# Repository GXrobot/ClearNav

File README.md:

GitHub Repository for Capstone Project of ClearNav Team
```
Members Include:
Spencer Lall
William Xue
Muhammad Ahmed Ather
William Huong
Namsakhi Kumar
Taimoor Ahmed
```

Spring - Summer 2022 Engineering Science Capstone Project

EZhud is a convenient heads up display motorcycle riders that features
built-in navigation, speed limit display and helmet mounted dashcam.

In this repository contains the code for the webserver, raspberry pi internal scripts
3D printed designs and GPS tracking code. 

EZhud is easy to use and and presents a simple interface for the user. Any information is presented in a heads up display above the riders right eye.

The following image shows the system overview of the EZhud device.

Here is a final product image on a full-face helmet.

The following is the Youtube video of the project.

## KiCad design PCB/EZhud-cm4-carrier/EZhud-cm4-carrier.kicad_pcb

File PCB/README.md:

PCB Design for EZhud Motorcycle Project

```
Lead by:
Muhammad Ahmed Ather
Taimoor Ahmed
```

PCB design is compact and meant to be connected to the Raspberry Pi CM4 board, featuring
all the ports necessary for our project. Including RPi CM4 Hirose connectors, high speed USB,
SD card slot, GPIO connectors, mini-HDMI connector, USB-C power connector and the RPi Cam
interface

Work is still in progress! PCB still needs some tweaking to be fully functional. 

This image shows the front of the PCB design.

This image shows the back of the PCB design.

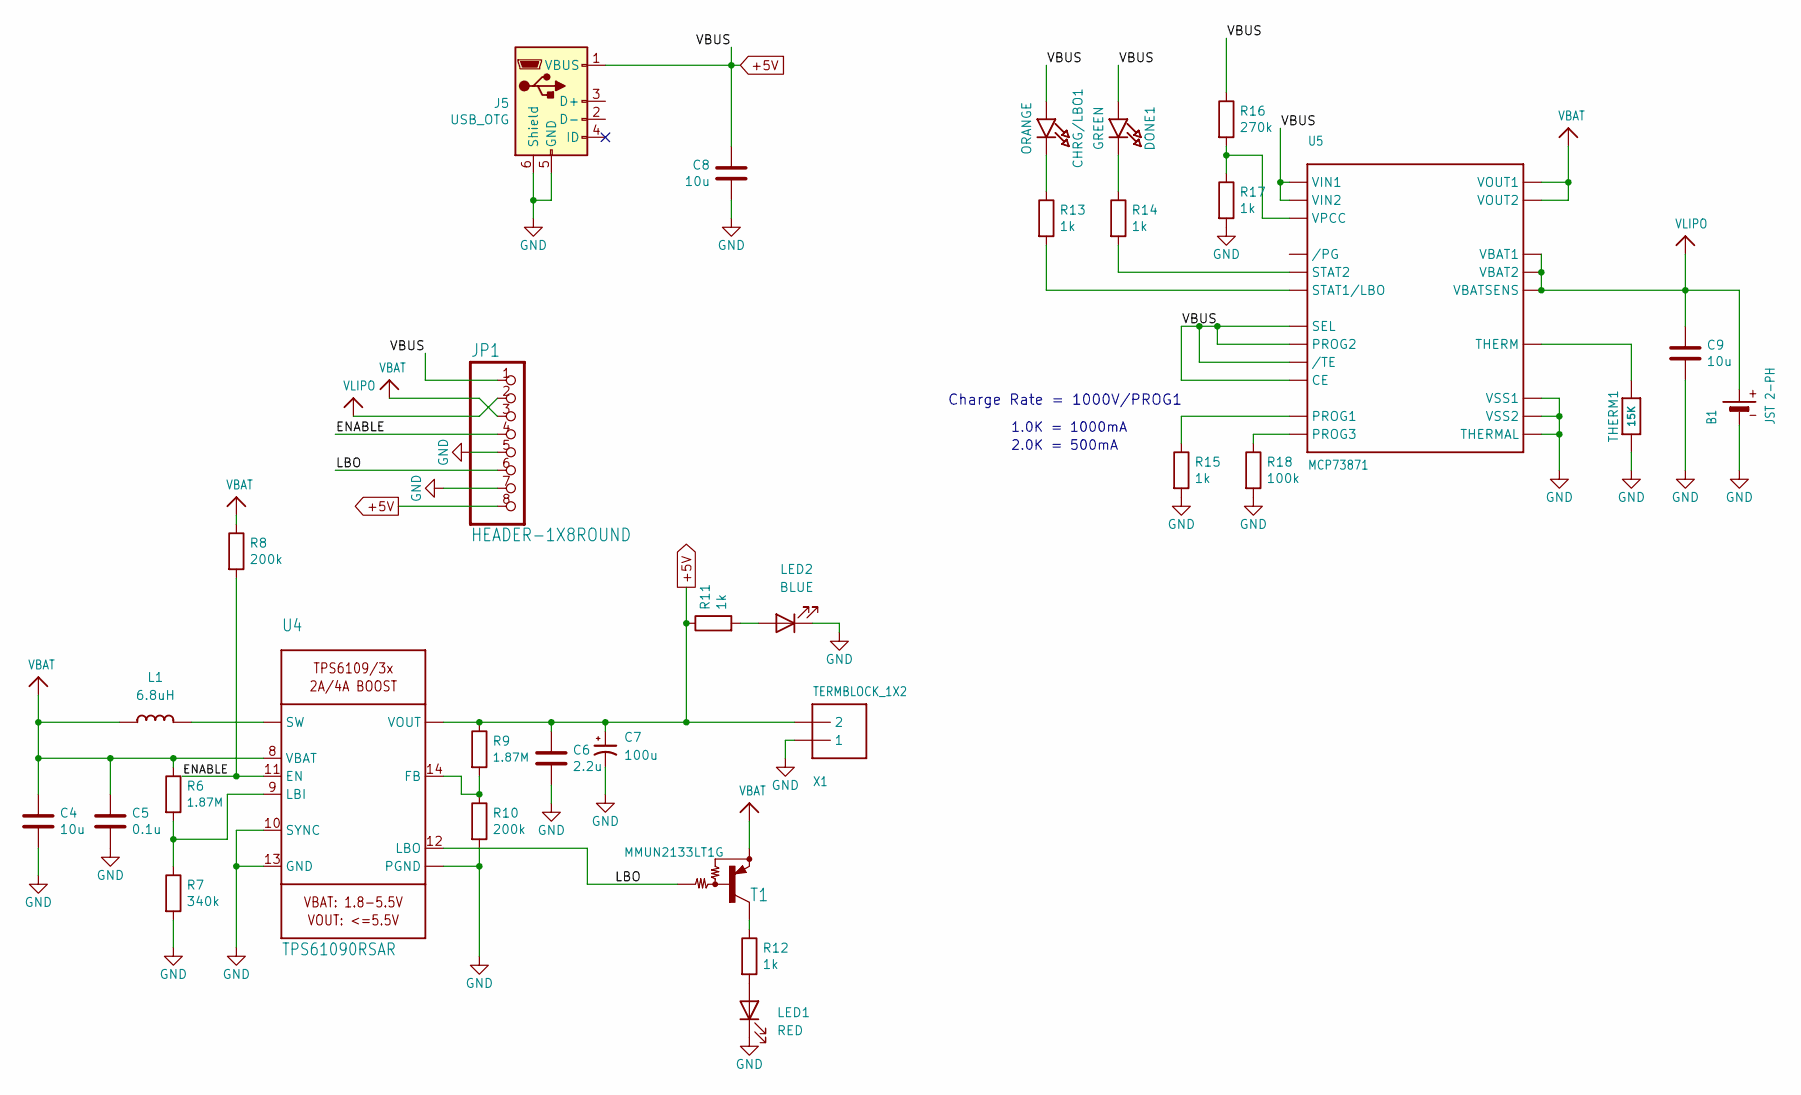
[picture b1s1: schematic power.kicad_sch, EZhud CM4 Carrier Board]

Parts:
B1: JST 2-PH; JSTPH2
C4, C8, C9: 10u; C_0805_2012Metric; Part Description 10uF 10% 10V Ceramic Capacitor X7R 0805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
C5: 0.1u; C_0805_2012Metric; Part Description 10uF 10% 10V Ceramic Capacitor X7R 0805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
C6: 2.2u; C_0805_2012Metric; Part Description 10uF 10% 10V Ceramic Capacitor X7R 0805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
C7: 100u; C_1210_3225Metric
CHRG/LBO1: ORANGE; CHIPLED_0805_NOOUTLINE
DONE1: GREEN; CHIPLED_0805_NOOUTLINE
J5: USB_OTG; USB_Micro-B_EDAC_UCON00686; Part Description USB - micro B USB 2.0 Receptacle Connec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
JP1: HEADER-1X8ROUND; 1X08_ROUND
L1: 6.8uH; INDUCTOR_5X5MM_TDK_VLC5045
LED1: RED; LED_0805_2012Metric
LED2: BLUE; LED_0805_2012Metric
R6, R9: 1.87M; R_0805_2012Metric
R7: 340k; R_0805_2012Metric
R8, R10: 200k; R_0805_2012Metric
R11, R12, R13, R14, R15, R17: 1k; R_0402_1005Metric; Part Description Resistor 1K M1005 1% 63mW
R16: 270k; R_0402_1005Metric; Part Description Resistor 1K M1005 1% 63mW
R18: 100k; R_0402_1005Metric; Part Description Resistor 1K M1005 1% 63mW
T1: MMUN2133LT1G; SC59-BEC
THERM1: 15K; 0805-NO
U4: TPS61090RSAR; PVQFN-16
U5: MCP73871; QFN20_4MM
X1: TERMBLOCK_1X2; TERMBLOCK_1X2-3.5MM

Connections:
+5V: C6.1, C7.1, C8.1, CHRG/LBO1.A, DONE1.A, J5.1 (VBUS), JP1.1, JP1.8, R9.1, R11.1, R16.1, U4.1 (VOUT), U4.15 (VOUT), U4.16 (VOUT), U5.P$3 (SEL), U5.P$4 (PROG2), U5.P$9 (/TE), U5.P$17 (CE), U5.P$18 (VIN1), U5.P$19 (VIN2), X1.2; also elsewhere on the board
/Power Boost/ENABLE: JP1.4, R8.2, U4.11 (EN)
/Power Boost/LBO: JP1.6, T1.B, U4.12 (LBO)
GND: B1.1 (-), C4.2, C5.2, C6.2, C7.2, C8.2, C9.2, J5.5 (GND), J5.6 (Shield), JP1.5, JP1.7, LED1.1 (K), LED2.1 (K), R7.2, R10.2, R15.2, R17.2, R18.2, THERM1.1, U4.5 (PGND), U4.6 (PGND), U4.7 (PGND), U4.10 (SYNC), U4.13 (GND), U4.P$18 (PGND), U4.P$19 (PGND), U4.P$20 (PGND), U4.P$21 (PGND), U4.P$22 (PGND), U4.THERMAL (PGND), U5.P$10 (VSS1), U5.P$11 (VSS2), U5.P$21 (THERMAL), X1.1; also elsewhere on the board
unnamed: CHRG/LBO1.C, R13.1
unnamed: DONE1.C, R14.1
unnamed: L1.P$2 (2), U4.3 (SW), U4.4 (SW)
unnamed: LED1.2 (A), R12.2
unnamed: LED2.2 (A), R11.2
unnamed: R6.2, R7.1, U4.9 (LBI)
unnamed: R9.2, R10.1, U4.14 (FB)
unnamed: R12.1, T1.C
unnamed: R13.2, U5.P$8 (STAT1/LBO)
unnamed: R14.2, U5.P$7 (STAT2)
unnamed: R15.1, U5.P$13 (PROG1)
unnamed: R16.2, R17.1, U5.P$2 (VPCC)
unnamed: R18.1, U5.P$12 (PROG3)
unnamed: THERM1.2, U5.P$5 (THERM)
VBAT: C4.1, C5.1, JP1.3, L1.P$1 (1), R6.1, R8.1, T1.E, U4.8 (VBAT), U5.P$1 (VOUT1), U5.P$20 (VOUT2)
VLIPO: B1.2 (+), C9.1, JP1.2, U5.P$14 (VBAT1), U5.P$15 (VBAT2), U5.P$16 (VBATSENS)

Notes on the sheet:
2.0K = 500mA
Charge Rate = 1000V/PROG1
1.0K = 1000mA

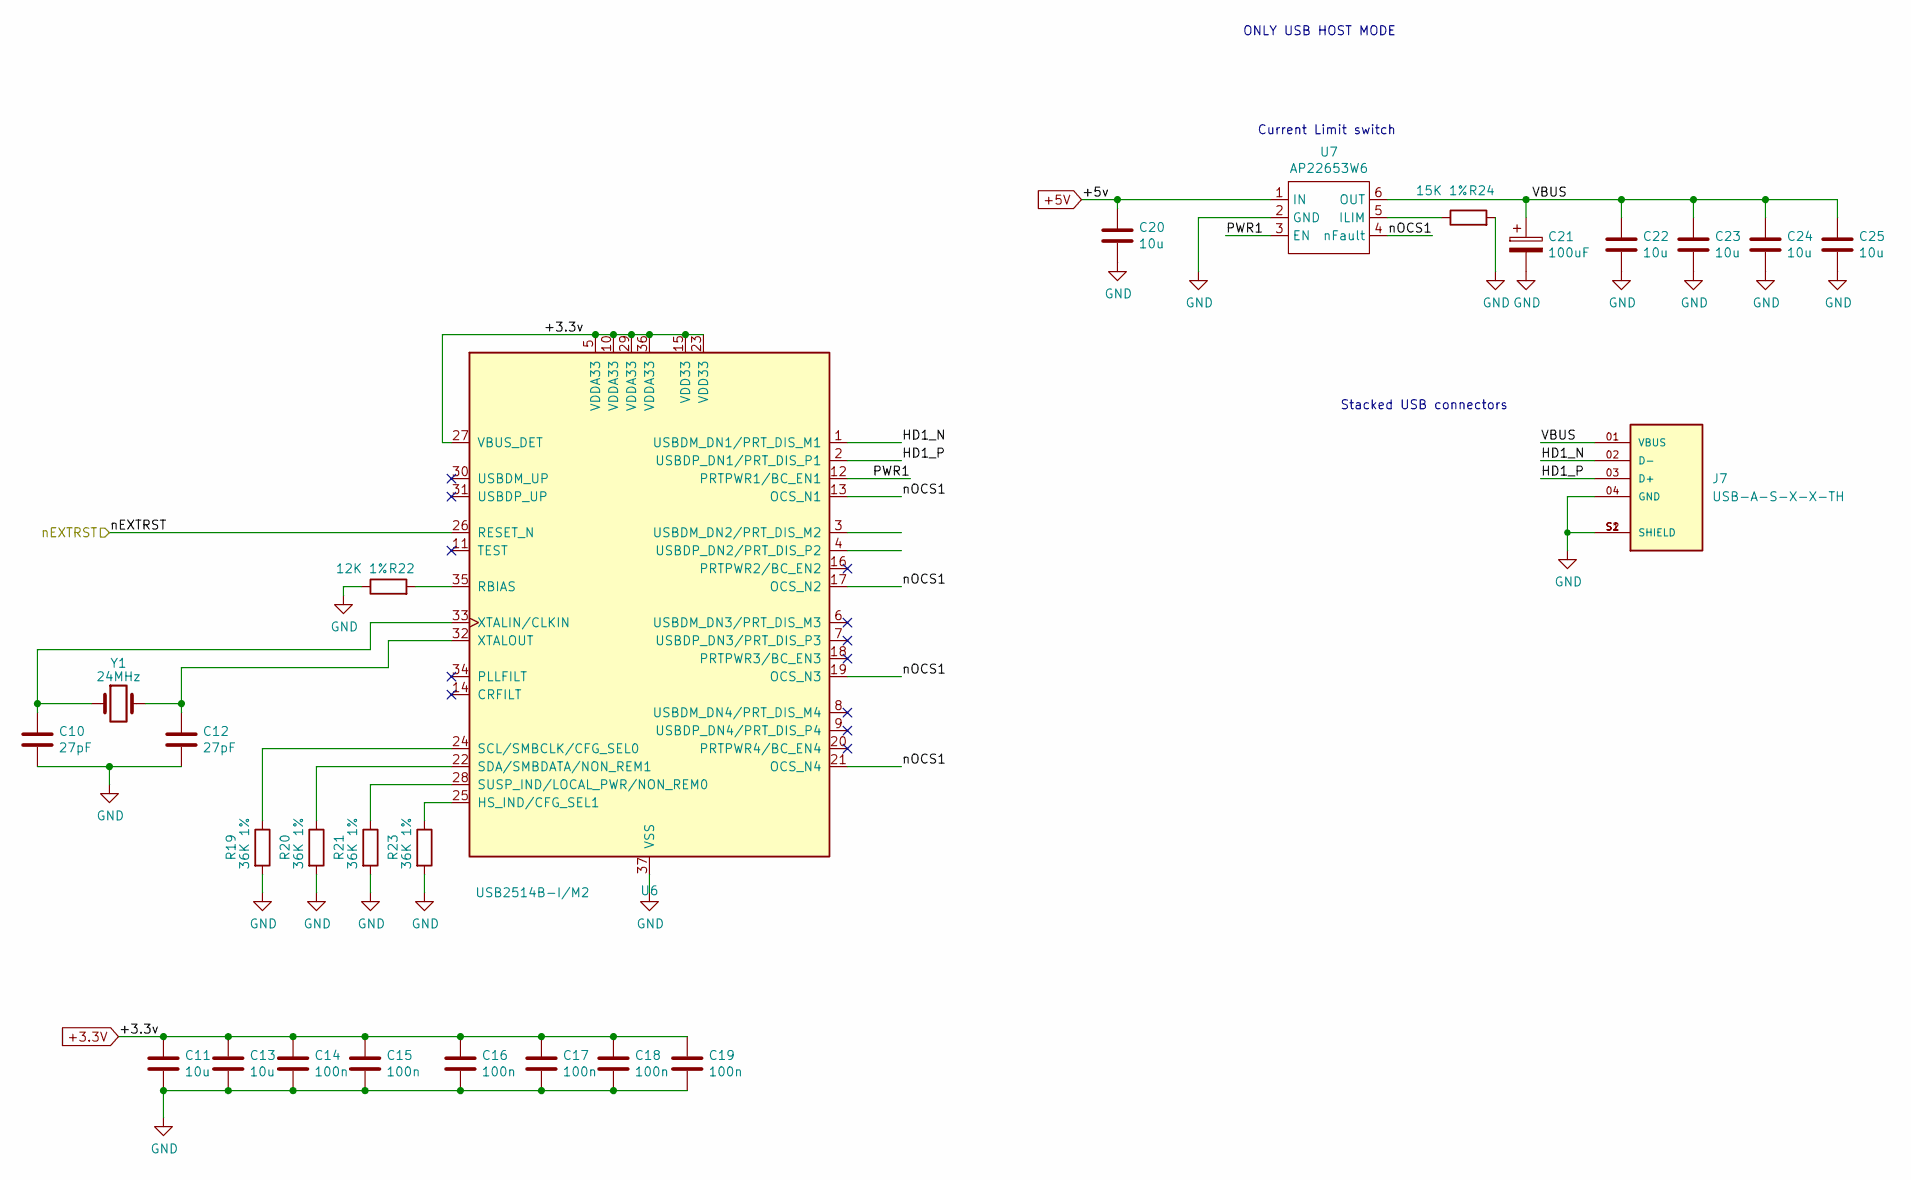
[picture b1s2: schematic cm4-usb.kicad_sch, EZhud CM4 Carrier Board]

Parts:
C10, C12: 27pF; C_0402_1005Metric; Part Description 27pF 5% 50V Ceramic Capacitor C0G, NP0 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
C11, C13, C20, C22, C23, C24, C25: 10u; C_0805_2012Metric; Part Description 10uF 10% 10V Ceramic Capacitor X7R 0805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
C14, C15, C16, C17, C18, C19: 100n; C_0402_1005Metric; Part Description 0.1uF 10% 16V Ceramic Capacitor X7R 040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
C21: 100uF; CP_EIA-7343-31_Kemet-D; Part Description Capacitor, SP-Cap, 100u, 6.3V, 15mR ESR
J7: USB-A-S-X-X-TH; SAMTEC_USB-A-S-X-X-TH; PARTREV R
R19, R20, R21, R23: 36K 1%; R_0402_1005Metric; Part Description Resistor 36K M1005 1% 63mW
R22: 12K 1%; R_0402_1005Metric; Part Description Resistor 12K M1005 1% 63mW
R24: 15K 1%; R_0402_1005Metric; Part Description Resistor 15K M1005 1% 63mW
U6: USB2514B-I/M2; QFN-36-1EP_6x6mm_P0.5mm_EP3.7x3.7mm; Part Description USB Hub Controller USB Interface 36-SQF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
U7: AP22653W6; SOT-23-6; Part Description Power Switch/Driver 1:1 P-Channel 2.1A 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
Y1: 24MHz; Crystal_SMD_HC49-SD; Part Description 24MHz Crystal 18pf 30ppm 30ppm

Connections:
+3.3V: C11.1, C13.1, C14.1, C15.1, C16.1, C17.1, C18.1, C19.1, U6.5 (VDDA33), U6.10 (VDDA33), U6.15 (VDD33), U6.23 (VDD33), U6.27 (VBUS_DET), U6.29 (VDDA33), U6.36 (VDDA33); also elsewhere on the board
+5V: C20.1, U7.1 (IN); also elsewhere on the board
/CM4 USB/HD1_N: J7.02 (D-), U6.1 (USBDM_DN1/PRT_DIS_M1)
/CM4 USB/HD1_P: J7.03 (D+), U6.2 (USBDP_DN1/PRT_DIS_P1)
/CM4 USB/PWR1: U6.12 (PRTPWR1/BC_EN1), U7.3 (EN)
/CM4 USB/VBUS: C21.1, C22.1, C23.1, C24.1, C25.1, J7.01 (VBUS), U7.6 (OUT)
/CM4 USB/nEXTRST: U6.26 (RESET_N)
/CM4 USB/nOCS1: U6.13 (OCS_N1), U6.17 (OCS_N2), U6.19 (OCS_N3), U6.21 (OCS_N4), U7.4 (nFault)
GND: C10.2, C11.2, C12.2, C13.2, C14.2, C15.2, C16.2, C17.2, C18.2, C19.2, C20.2, C21.2, C22.2, C23.2, C24.2, C25.2, J7.04 (GND), J7.S1 (SHIELD), J7.S2 (SHIELD), R19.2, R20.2, R21.2, R22.1, R23.2, R24.2, U6.37 (VSS), U7.2 (GND); also elsewhere on the board
unnamed: C10.1, U6.33 (XTALIN/CLKIN), Y1.1
unnamed: C12.1, U6.32 (XTALOUT), Y1.2
unnamed: R19.1, U6.24 (SCL/SMBCLK/CFG_SEL0)
unnamed: R20.1, U6.22 (SDA/SMBDATA/NON_REM1)
unnamed: R21.1, U6.28 (SUSP_IND/LOCAL_PWR/NON_REM0)
unnamed: R22.2, U6.35 (RBIAS)
unnamed: R23.1, U6.25 (HS_IND/CFG_SEL1)
unnamed: R24.1, U7.5 (ILIM)

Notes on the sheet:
Current Limit switch
Stacked USB connectors
ONLY USB HOST MODE

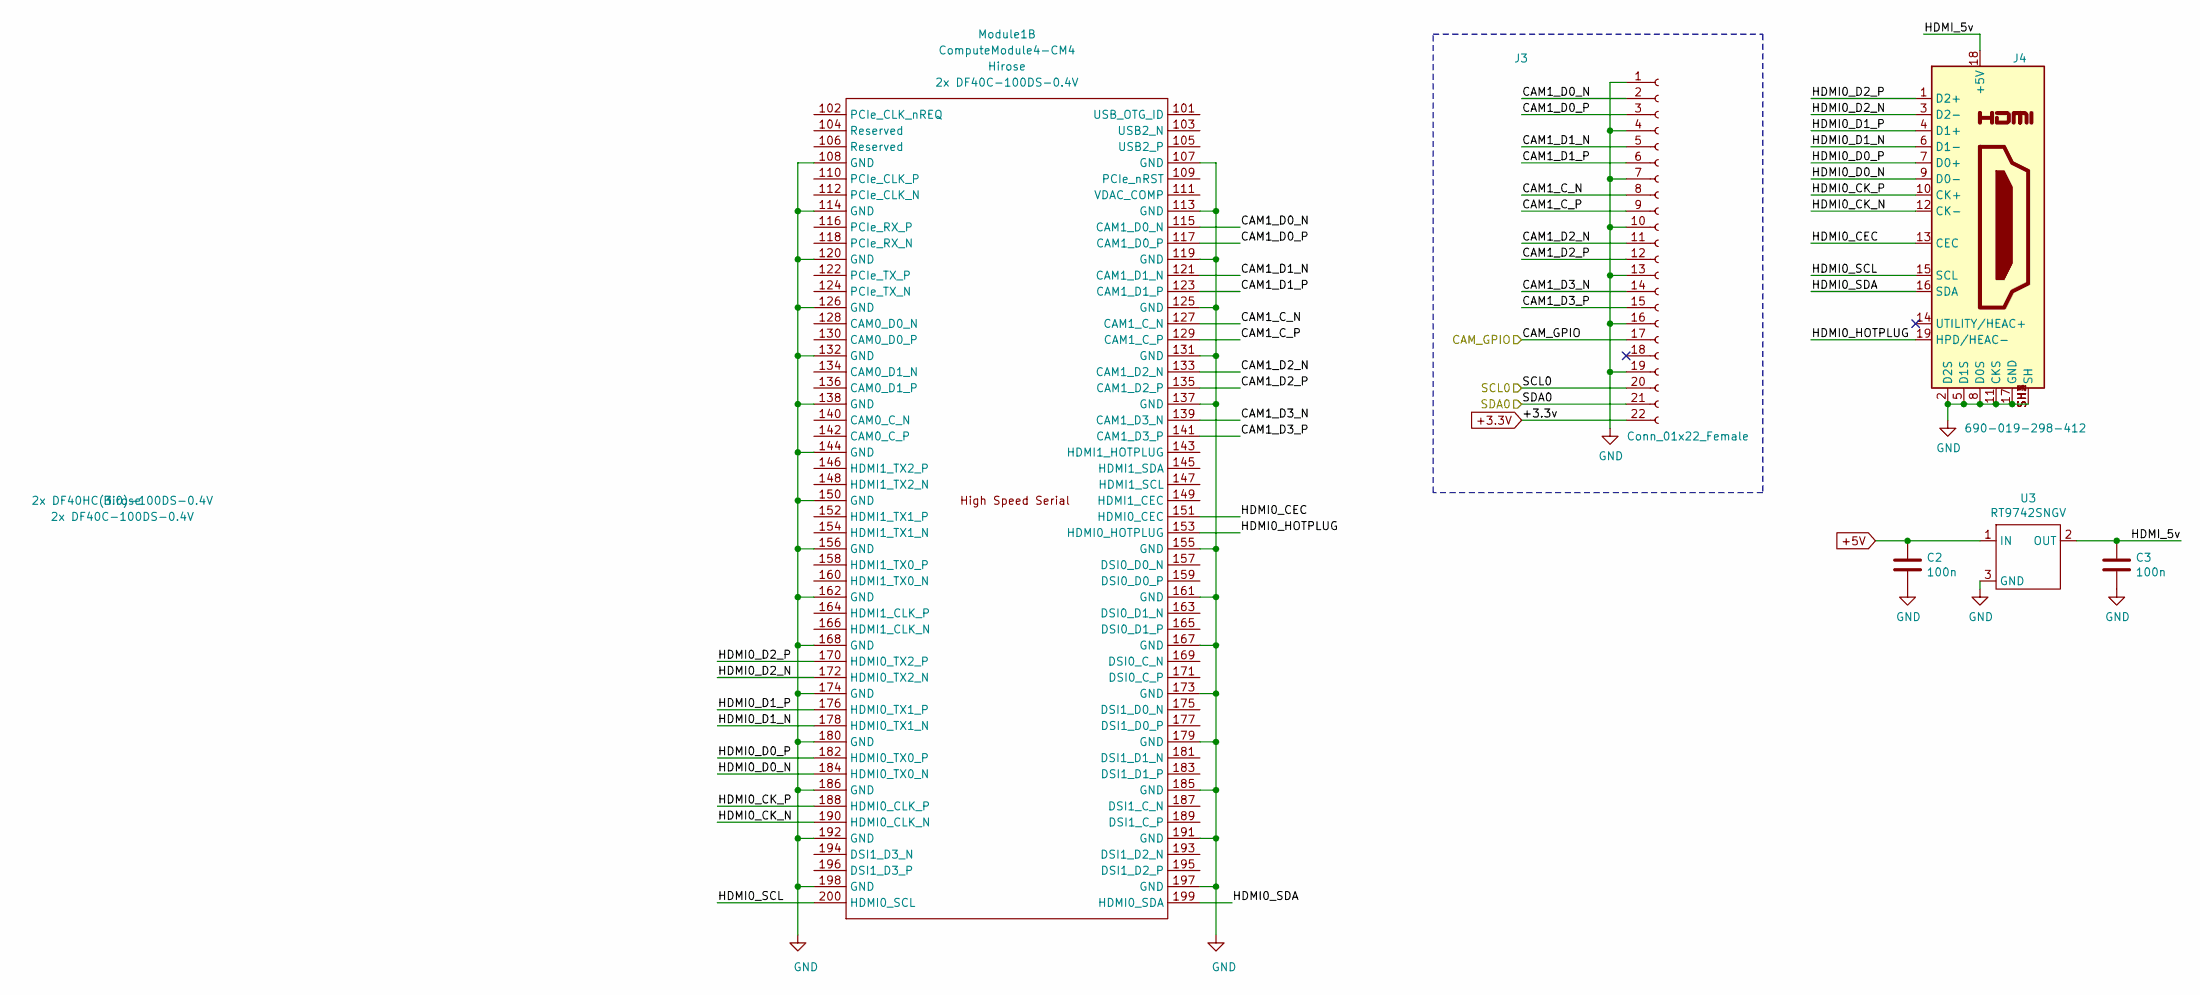
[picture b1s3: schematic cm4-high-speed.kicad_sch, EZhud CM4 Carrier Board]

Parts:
C2, C3: 100n; C_0402_1005Metric; Part Description 0.1uF 10% 16V Ceramic Capacitor X7R 040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
J3: Conn_01x22_Female; Hirose_FH12-22S-0.5SH_1x22-1MP_P0.50mm_Horizontal; Part Description 22 Position FFC, FPC Connector Contacts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
J4: 690-019-298-412; EDAC 690-019-298-412; Part Description HDMI Connector, Right Angle, 19 Contact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
Module1: ComputeModule4-CM4; Raspberry-Pi-4-Compute-Module; MPN 2x DF40C-100DS-0.4V; Digi-Key_PN 2x H11615CT-ND
U3: RT9742SNGV; SOT-23; Part Description Power Switch/Driver 1:1 N-Channel 500mA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

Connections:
+3.3V: J3.22; also elsewhere on the board
+5V: C2.1, U3.1 (IN); also elsewhere on the board
/CM4 High Speed/CAM1_C_N: J3.8, Module1.127 (CAM1_C_N)
/CM4 High Speed/CAM1_C_P: J3.9, Module1.129 (CAM1_C_P)
/CM4 High Speed/CAM1_D0_N: J3.2, Module1.115 (CAM1_D0_N)
/CM4 High Speed/CAM1_D0_P: J3.3, Module1.117 (CAM1_D0_P)
/CM4 High Speed/CAM1_D1_N: J3.5, Module1.121 (CAM1_D1_N)
/CM4 High Speed/CAM1_D1_P: J3.6, Module1.123 (CAM1_D1_P)
/CM4 High Speed/CAM1_D2_N: J3.11, Module1.133 (CAM1_D2_N)
/CM4 High Speed/CAM1_D2_P: J3.12, Module1.135 (CAM1_D2_P)
/CM4 High Speed/CAM1_D3_N: J3.14, Module1.139 (CAM1_D3_N)
/CM4 High Speed/CAM1_D3_P: J3.15, Module1.141 (CAM1_D3_P)
/CM4 High Speed/CAM_GPIO: J3.17; also elsewhere on the board
/CM4 High Speed/HDMI0_CEC: J4.13 (CEC), Module1.151 (HDMI0_CEC)
/CM4 High Speed/HDMI0_CK_N: J4.12 (CK-), Module1.190 (HDMI0_CLK_N)
/CM4 High Speed/HDMI0_CK_P: J4.10 (CK+), Module1.188 (HDMI0_CLK_P)
/CM4 High Speed/HDMI0_D0_N: J4.9 (D0-), Module1.184 (HDMI0_TX0_N)
/CM4 High Speed/HDMI0_D0_P: J4.7 (D0+), Module1.182 (HDMI0_TX0_P)
/CM4 High Speed/HDMI0_D1_N: J4.6 (D1-), Module1.178 (HDMI0_TX1_N)
/CM4 High Speed/HDMI0_D1_P: J4.4 (D1+), Module1.176 (HDMI0_TX1_P)
/CM4 High Speed/HDMI0_D2_N: J4.3 (D2-), Module1.172 (HDMI0_TX2_N)
/CM4 High Speed/HDMI0_D2_P: J4.1 (D2+), Module1.170 (HDMI0_TX2_P)
/CM4 High Speed/HDMI0_HOTPLUG: J4.19 (HPD/HEAC-), Module1.153 (HDMI0_HOTPLUG)
/CM4 High Speed/HDMI0_SCL: J4.15 (SCL), Module1.200 (HDMI0_SCL)
/CM4 High Speed/HDMI0_SDA: J4.16 (SDA), Module1.199 (HDMI0_SDA)
/CM4 High Speed/HDMI_5v: C3.1, J4.18 (+5V), U3.2 (OUT)
/CM4 High Speed/SCL0: J3.20; also elsewhere on the board
/CM4 High Speed/SDA0: J3.21; also elsewhere on the board
GND: C2.2, C3.2, J3.1, J3.4, J3.7, J3.10, J3.13, J3.16, J3.19, J4.2 (D2S), J4.5 (D1S), J4.8 (D0S), J4.11 (CKS), J4.17 (GND), J4.SH1 (SH), J4.SH2 (SH), J4.SH3 (SH), J4.SH4 (SH), Module1.107 (GND), Module1.108 (GND), Module1.113 (GND), Module1.114 (GND), Module1.119 (GND), Module1.120 (GND), Module1.125 (GND), Module1.126 (GND), Module1.131 (GND), Module1.132 (GND), Module1.137 (GND), Module1.138 (GND), Module1.144 (GND), Module1.150 (GND), Module1.155 (GND), Module1.156 (GND), Module1.161 (GND), Module1.162 (GND), Module1.167 (GND), Module1.168 (GND), Module1.173 (GND), Module1.174 (GND), Module1.179 (GND), Module1.180 (GND), Module1.185 (GND), Module1.186 (GND), Module1.191 (GND), Module1.192 (GND), Module1.197 (GND), Module1.198 (GND), U3.3 (GND); also elsewhere on the board

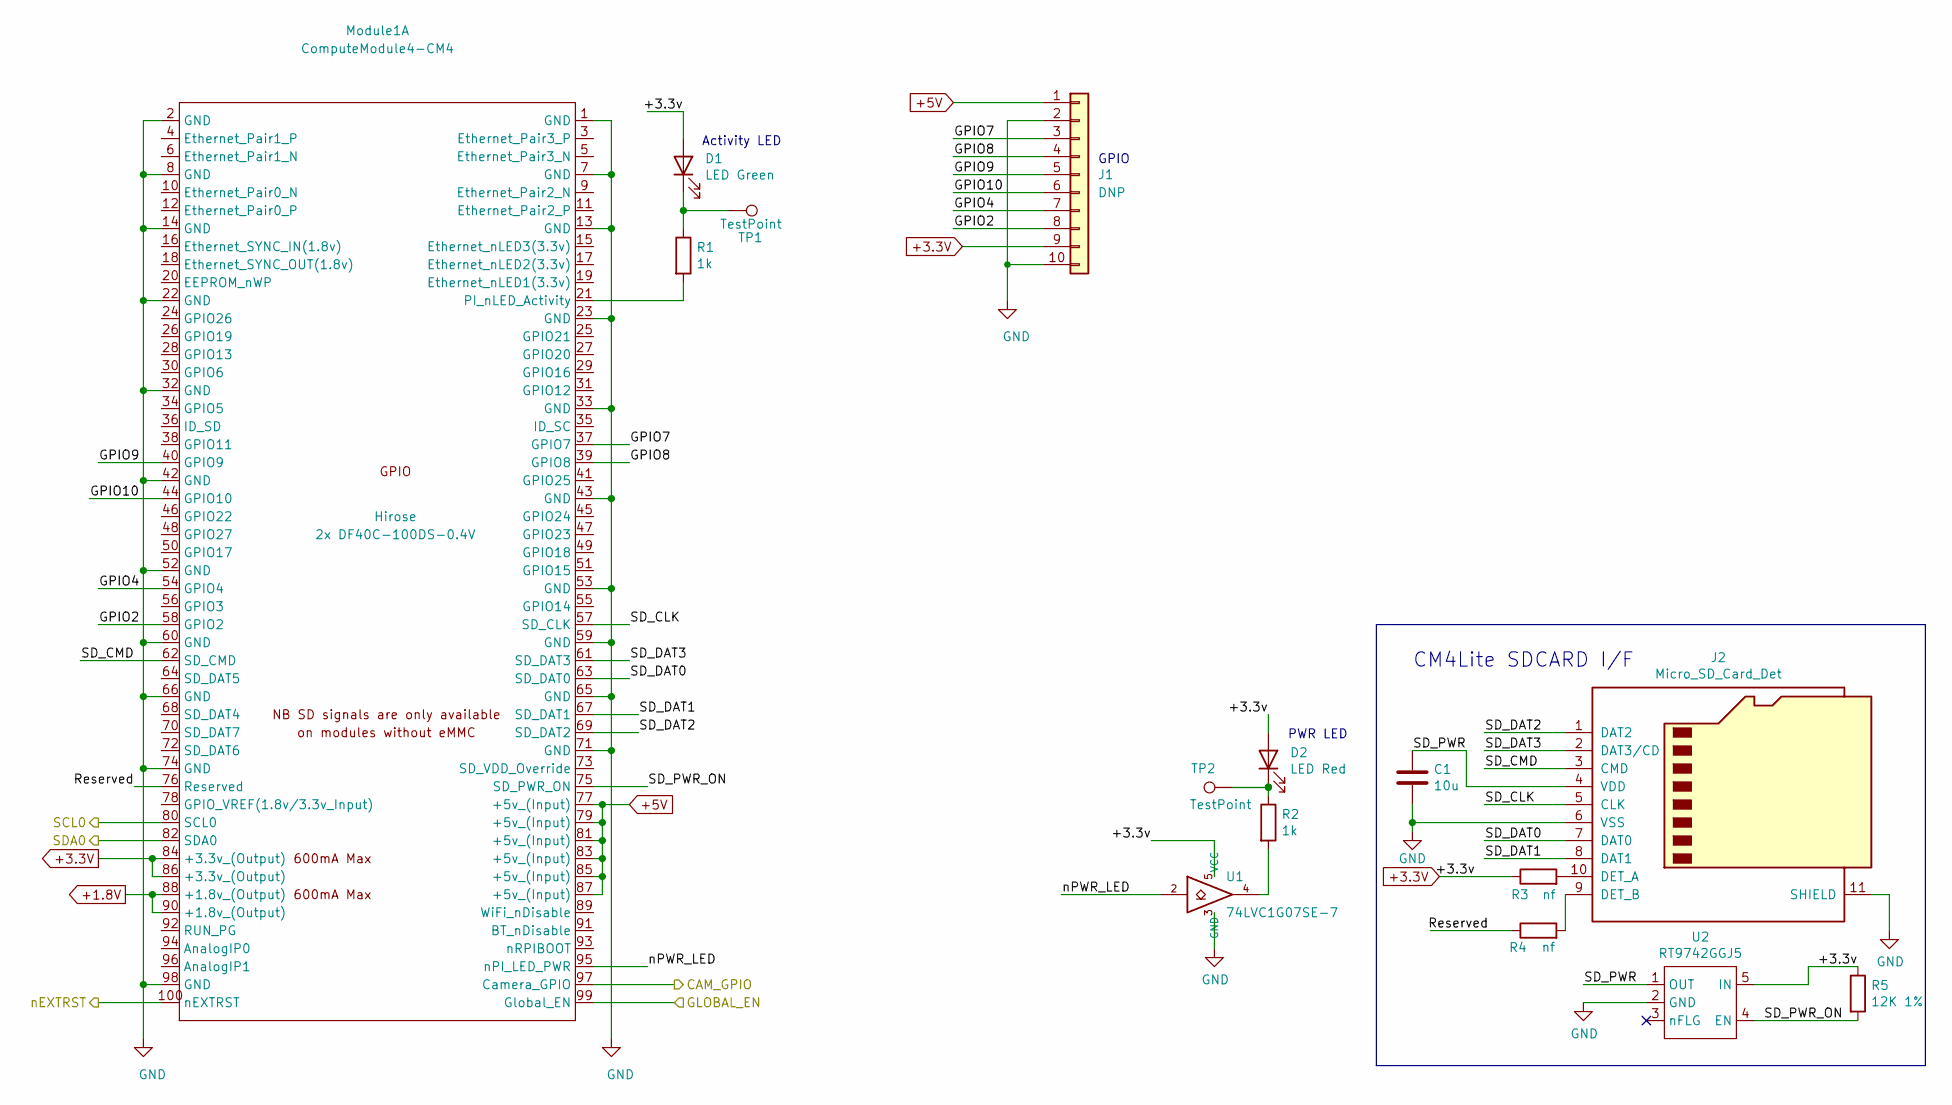
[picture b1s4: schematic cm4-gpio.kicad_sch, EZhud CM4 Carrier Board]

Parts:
C1: 10u; C_0805_2012Metric; Part Description 10uF 10% 10V Ceramic Capacitor X7R 0805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
D1: LED Green; LED_0603_1608Metric; Part Description Green 572nm LED Indication - Discrete 2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
D2: LED Red; LED_0603_1608Metric; Part Description Red 620nm LED Indication - Discrete 2.2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
J1: DNP; PinHeader_1x10_P2.54mm_Vertical
J2: Micro_SD_Card_Det; SDCARD_MOLEX_503398-1892; Part Description 9 (8 + 1) Position Card Connector micro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
Module1: ComputeModule4-CM4; Raspberry-Pi-4-Compute-Module; MPN 2x DF40C-100DS-0.4V; Digi-Key_PN 2x H11615CT-ND
R1, R2: 1k; R_0402_1005Metric; Part Description Resistor 1K M1005 1% 63mW
R3, R4: nf; R_0402_1005Metric; Part Description Resistor 1K M1005 1% 63mW
R5: 12K 1%; R_0402_1005Metric; Part Description Resistor 12K M1005 1% 63mW
TP1, TP2: TestPoint; TestPoint_Pad_2.0x2.0mm
U1: 74LVC1G07SE-7; SOT-353_SC-70-5; Part Description Buffer, Non-Inverting 1 Element 1 Bit p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
U2: RT9742GGJ5; SOT-23-5; Part Description Power Switch/Driver 1:1 N-Channel 1A TS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

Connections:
+1.8V: Module1.88 (+1.8v_(Output)), Module1.90 (+1.8v_(Output))
+3.3V: D1.2 (A), D2.2 (A), J1.9, Module1.84 (+3.3v_(Output)), Module1.86 (+3.3v_(Output)), R3.1, R5.1, U1.5 (VCC), U2.5 (IN); also elsewhere on the board
+5V: J1.1, Module1.77 (+5v_(Input)), Module1.79 (+5v_(Input)), Module1.81 (+5v_(Input)), Module1.83 (+5v_(Input)), Module1.85 (+5v_(Input)), Module1.87 (+5v_(Input)); also elsewhere on the board
/CM4 GPIO/GLOBAL_EN: Module1.99 (Global_EN)
/CM4 GPIO/GPIO2: J1.8, Module1.58 (GPIO2)
/CM4 GPIO/GPIO4: J1.7, Module1.54 (GPIO4)
/CM4 GPIO/GPIO7: J1.3, Module1.37 (GPIO7)
/CM4 GPIO/GPIO8: J1.4, Module1.39 (GPIO8)
/CM4 GPIO/GPIO9: J1.5, Module1.40 (GPIO9)
/CM4 GPIO/GPIO10: J1.6, Module1.44 (GPIO10)
/CM4 GPIO/Reserved: Module1.76 (Reserved), R4.1
/CM4 GPIO/SD_CLK: J2.5 (CLK), Module1.57 (SD_CLK)
/CM4 GPIO/SD_CMD: J2.3 (CMD), Module1.62 (SD_CMD)
/CM4 GPIO/SD_DAT0: J2.7 (DAT0), Module1.63 (SD_DAT0)
/CM4 GPIO/SD_DAT1: J2.8 (DAT1), Module1.67 (SD_DAT1)
/CM4 GPIO/SD_DAT2: J2.1 (DAT2), Module1.69 (SD_DAT2)
/CM4 GPIO/SD_DAT3: J2.2 (DAT3/CD), Module1.61 (SD_DAT3)
/CM4 GPIO/SD_PWR: C1.1, J2.4 (VDD), U2.1 (OUT)
/CM4 GPIO/SD_PWR_ON: Module1.75 (SD_PWR_ON), R5.2, U2.4 (EN)
/CM4 GPIO/nEXTRST: Module1.100 (nEXTRST)
/CM4 GPIO/nPWR_LED: Module1.95 (nPI_LED_PWR), U1.2
/CM4 High Speed/CAM_GPIO: Module1.97 (Camera_GPIO); also elsewhere on the board
/CM4 High Speed/SCL0: Module1.80 (SCL0); also elsewhere on the board
/CM4 High Speed/SDA0: Module1.82 (SDA0); also elsewhere on the board
GND: C1.2, J1.2, J1.10, J2.6 (VSS), J2.11 (SHIELD), Module1.1 (GND), Module1.2 (GND), Module1.7 (GND), Module1.8 (GND), Module1.13 (GND), Module1.14 (GND), Module1.22 (GND), Module1.23 (GND), Module1.32 (GND), Module1.33 (GND), Module1.42 (GND), Module1.43 (GND), Module1.52 (GND), Module1.53 (GND), Module1.59 (GND), Module1.60 (GND), Module1.65 (GND), Module1.66 (GND), Module1.71 (GND), Module1.74 (GND), Module1.98 (GND), U1.3 (GND), U2.2 (GND); also elsewhere on the board
unnamed: D1.1 (K), R1.1, TP1.1
unnamed: D2.1 (K), R2.1, TP2.1
unnamed: J2.9 (DET_B), R4.2
unnamed: J2.10 (DET_A), R3.2
unnamed: Module1.21 (PI_nLED_Activity), R1.2
unnamed: R2.2, U1.4

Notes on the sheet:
PWR LED
CM4Lite SDCARD I/F
Activity LED
GPIO

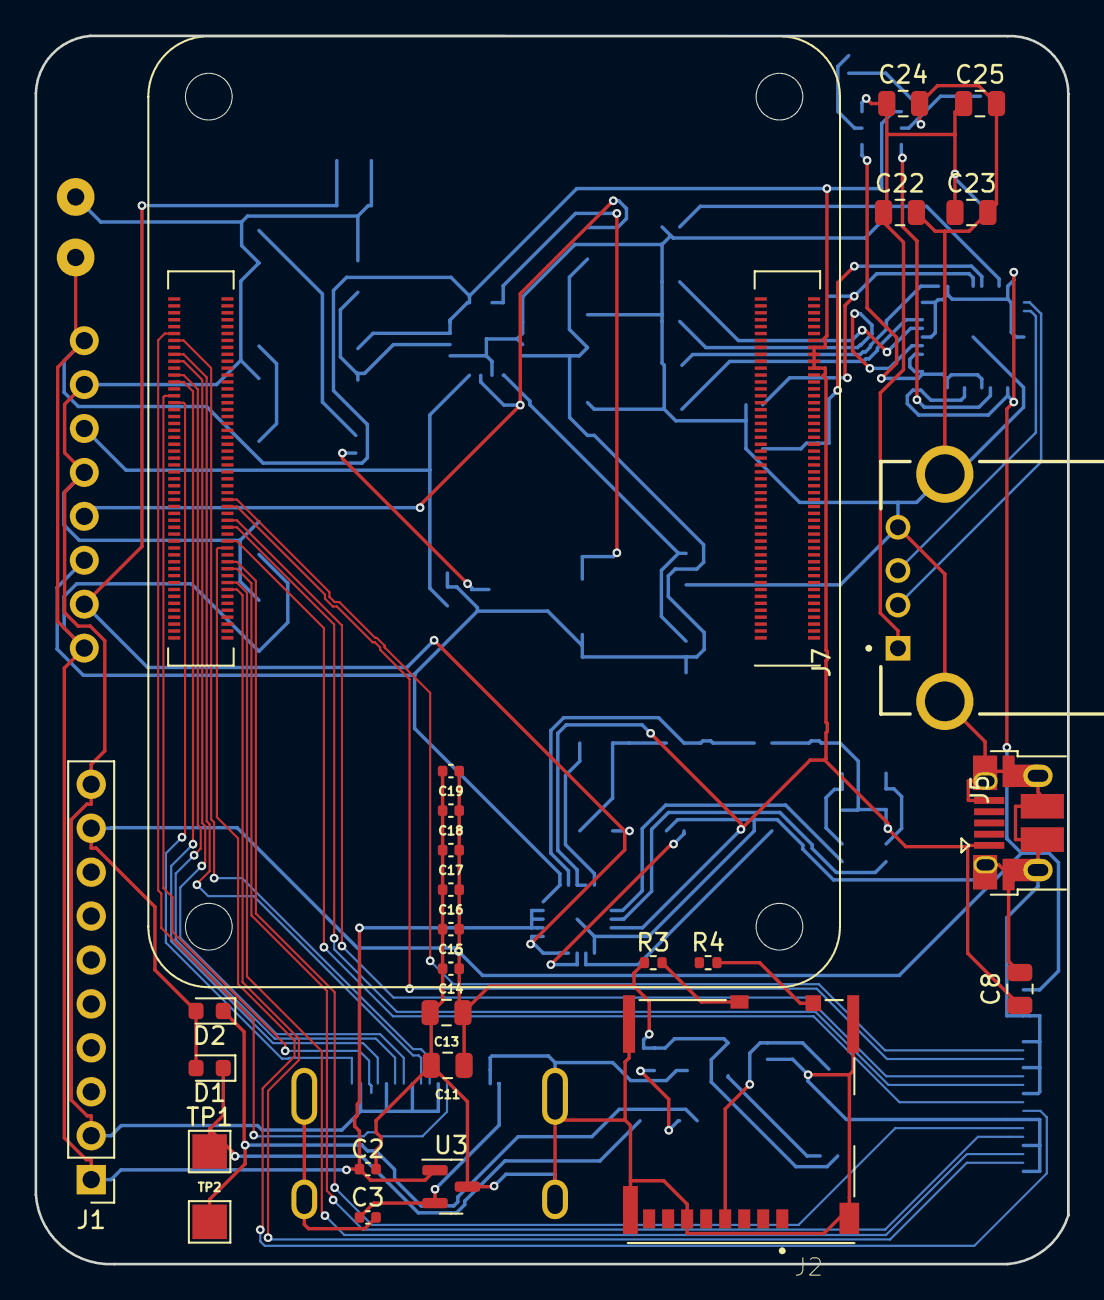
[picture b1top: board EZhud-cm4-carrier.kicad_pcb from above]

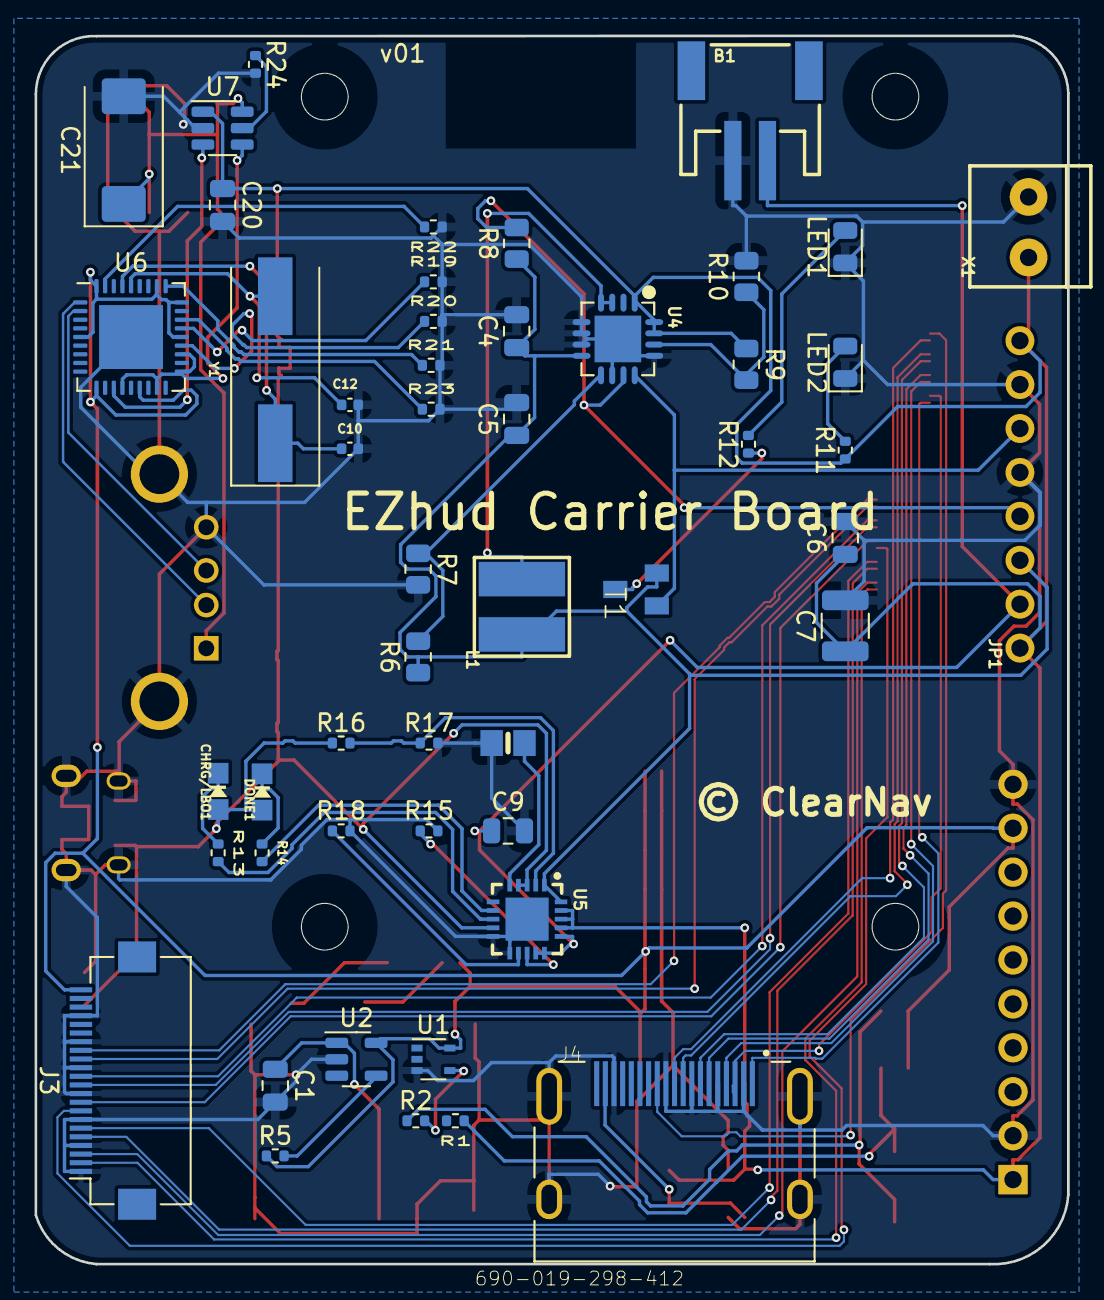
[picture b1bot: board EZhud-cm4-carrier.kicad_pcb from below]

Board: 2 copper layers, 59.7 x 71.0 mm, 78 parts (51 on the bottom side), 83 nets.

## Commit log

2022-03-22 Adding initial webserver
2022-03-23 Updated routes
2022-03-23 Start Navigation Button
2022-03-23 Settings Page -First Draft
2022-03-23 settings page first draft
2022-03-23 Revert "settings page first draft"
    This reverts commit 29e3c216a7655569313222b47aa14462ecb8ab52.
2022-03-23 added seeting page - first draft and assets
2022-03-25 Updated settings pg - new files -linked index.html
2022-03-27 navigation autocomplete working
2022-03-27 map with marker working
2022-03-28 Settings and Battery status page - done
2022-03-28 settings and battery status pages - done
2022-03-31 added debug mode
2022-03-31 fixed broken buttons
2022-04-02 Adding stubs for settings
2022-04-02 Working getWifiMode()
2022-04-03 setEZhudSettings() working, adjusted comments
2022-04-03 added some css to elements
2022-04-03 Untested getWifiSSID(), setWifiMode()
2022-04-03 Adding readme for web server
2022-04-03 Tested getWifiSSID(), setWifiMode(), added setBrightnessMode(), getWifiCountry()
2022-04-04 Added setWifiCountry(), getBrightnessMode(), setEZhudSettings() now flushes changes to disk
2022-04-04 all pages work (on chrome lol)
2022-04-05 Finished all EZhudSettings functions, updated index.html and index.js for testing
2022-04-05 typo
2022-04-05 Set client wifi changes to force wpa_supplicant.conf regeneration
2022-04-05 Added reboot on Wifi changes
2022-04-05 Merging settings branch into poc_integration (#2)
    Merging PoC settings branch
2022-04-05 settings should send to server
2022-04-05 wifi_country fixed
2022-04-08 UI update + loading screen
2022-04-08 partially working
2022-04-09 chrome bad
2022-04-09 Unlock FS on web server start
2022-04-09 routes working
2022-04-09 Changed port from 8080 to 80
2022-04-09 Reverting port back to 8080 from 80
2022-04-09 Server now adjust baseUrl in index.js on startup
2022-04-10 maps modification
2022-04-10 Changed port to 80; service files added
2022-04-10 Minor typo
2022-04-10 Renamed web server setup script, now starts server
2022-04-10 Merge auto_start into poc_integration (#3)
    * Changed port to 80; service files added
    * Minor typo
    * Renamed web server setup script, now starts server
2022-04-10 Updated readme.md for auto-starting server
2022-04-10 Typo...
2022-06-29 gps info printing out to terminal only
2022-06-29 serial read with PySimpleGUI window
2022-07-24 Removing CrankShaft code from web server setup, startup
2022-07-25 Updated GPS code
2022-07-26 Making GUI GPS script executable
2022-07-26 Adding scripts. Most are WIP
2022-07-26 Initial, untested changes for OpenDash instead of CrankShaft
2022-07-27 New script that does most of the setup for EZhud
2022-07-28 Modified setup.sh to adjust the necessary settings. Untested
2022-07-28 Adding WaveShare CM4-NANO-B device tree
2022-07-29 Typos, some status echo's
2022-07-29 check_nw.sh pointed to wrong location for ap_mode.sh
2022-07-29 Removing log_stats.sh from starting on boot, doesn't work
2022-07-29 GPS UI size no longer hard-coded
2022-07-29 Updating delays on startup script
2022-07-29 setup.sh now hides menubar
2022-07-29 Potential fix for some commands not executing
2022-07-29 Forgot a couple of items to remove in /boot/config.txt
2022-07-29 Needed to bump up the wait time for GPS UI
2022-07-30 Removed port 8080 references, changed default IP in index.js to zero-conf addr
2022-07-30 Typo in wpa_supplicant.conf path
2022-07-30 Removing references to brightness since this is not controllable
2022-07-30 Removing get and set wifi mode, no longer applicable
2022-07-30 getWifiCountry() updated to read from wpa_cli
2022-07-30 pray for me
2022-07-31 Undoing some comments
2022-07-31 Server now sends list of videos
2022-07-31 updated gps gui
2022-07-31 getallvideoslist working
2022-07-31 getsinglevideo working
2022-07-31 cleanup
2022-07-31 fixed
2022-08-01 Initial changes to setup script, untested
2022-08-01 Changing menubar config path
2022-08-01 Added timzeone and wifi country set
2022-08-01 More echos
2022-08-01 Moving GPS scripts into the scripts directory
2022-08-01 navbar works offline now
2022-08-01 Correct lxpanel config file, hiding cursor
2022-08-01 Updated recording filenaming, change to 1 min clips
2022-08-01 Another typo...
2022-08-01 Changing timezone from LA to Vancouver
2022-08-01 Replacing code to determine server IP with location.hostname call client-side
2022-08-01 Making GPS scripts executable. Again
2022-08-02 Changing location.hostname call to window.location.origin
2022-08-02 Changing dt-blob.bin pathing from relative to absolute
2022-08-02 Accounting for space in filename in recordings router
2022-08-02 videos showing correct time on GUI now
2022-08-03 Fixing some errors from merge
2022-08-03 setup.sh now writes blank wpa_supplicant.conf
2022-08-03 ipaddress shown on gps GUI
2022-08-04 temp fix hehehe
2022-08-04 Removing API key, hard-coded baseUrl, debug set back to true
2022-08-04 ip_address update in loop
2022-08-04 recording script now sets and unsets flag file. Untested
2022-08-04 setup.sh now enables HDMI hotplug
2022-08-04 Fixing broken format string in record.py
2022-08-04 record.py removes the flag file when killed
2022-08-04 Forgot how Python works...
2022-08-04 changes to dashcam page
2022-08-04 Commenting out potentially problematic wpa_supplicant stuff in setup.sh
2022-08-04 added recording status to gui
2022-08-05 removed wifi mode from settings
2022-08-05 Adjusting GPIO pinouts, debounce time to match Gamma Prototype
2022-08-05 Setting bitrate for recording
2022-08-05 fixed settings
2022-08-05 Removing no longer used settings functions
2022-09-09 Starting the Vufine
2022-09-09 Adding 3D designs
2022-09-09 Adding images
2022-09-09 Adding README to 3D printing part
2022-09-09 README for main page
2022-10-21 Adding PCB design

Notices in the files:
PCB/EZhud-cm4-carrier/EZhud-cm4-carrier.kicad_pcb:
© ClearNav
